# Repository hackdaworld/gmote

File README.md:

# GMote
[GMote](https://digidev.de/gmote) - The Generic LoRaWAN Node

GMote stands for Generic Mote.
It is meant to be a flexible (i.e. applicable in different scenarios for different purposes utilizing different sensors) IoT Node using the LoRa wireless data communication technology. 

The first test version was based on the Arduino Pro Mini, which requires very low power if you remove the LED and bypass the power regulator.
Once this proved to be a good idea, a slim version of the Mini Pro board (i.e. the ATMega 328PB) has been integrated and routed on the GMote circuit board.
At first, the Dragino LoRa Bee was the transceiving unit since we had good results with respect to range and usability.
In later versions, the relevant HopeRF modem (RFM95) chip was likewise integrated on the board due to availability and price. 

There are two PCB versions, a small and a mini version, which provide different amount of pin headers to connect various sensors or even actuators. 
Development of an ARM Cortex M0 based version is in progress.

The node is configurable via UART and (planned) LoRaWAN download frames.

It started within the Arduino framework and, as far as the AVR version is concerned, will stick to it to not loose the huge developer community.

## Most important

GMote is meant to become an all-purpose LoRaWAN node (and in fact a whole eco system).
Moreover, the design, hardware, firmware and software of the GMote project is open source and free to use without any restriction.
To enable everyone to participate, everything is kept as simple as possible, ranging from the low-level PCB design and firmware up to the high-level IoT platform app.

Since it aims to become a project for a hopefully huge community, let the GMote developers know what you think about it, about problems that occured, additional features that you require and everything you would like to have changed in the current realization. 
Anything on your mind?
Maybe to remove the RTC in favor of the internal watchdog timer to make the board even more simple (thereby accepting some inaccuracy in the periodicity of frames)? 
No I2C pinout or at least another version without?
A voltage regulator for a well defined supply but a shorter battery lifetime in return?
Whatever it is, let us know!

## Requirements

* ISP programmer, e.g. the [Pocket AVR Programmer](https://www.digikey.de/product-detail/de/sparkfun-electronics/PGM-09825/1568-1080-ND/5230949), to upload the firmware or an optional Arduino bootloader as you please.
* USB to serial converter (3.3V), e.g. the [FT231X Breakout](https://www.digikey.de/product-detail/de/sparkfun-electronics/BOB-13263/1568-1720-ND/7675364) for optionally uploading the firmware the Arduino way (via boot loader) and for serial communication and configuration. Strictly speaking, this is not required, since you could configure the node (i.e. program the EEPROM) via ISP. However, it is strongly suggested!
* A board (see below) produced by your favorite PCB manufacturer.
* The parts listed in the respective bill of materials.
* Soldering iron and solder.

## Hardware

### PCB

There are currently two versions ([small](pcb/small) and [mini](pcb/mini)) of the GMote LoRaWAN node, which are based on the ATMega 328PB and run quite reliably.
Moreover, there is one based on the [ARM MCU](pcb/arm), which is in very early stage and comes without any guarantee to work. We mean it!

You can find the available PCBs in the respective [PCB](pcb) directory
together with further details as well as the bill of materials and respective [DigiKey](https://www.digikey.de/) part numbers.

The boards are designed with [KiCad](http://kicad.org/).
A lot of PCB manufacturers directly support the KiCad PCB files.

The size of the SMD parts was chosen to be 0805 (2012) and hand soldering pads were used for the resistors and capacitors so you can DIY at home with a low cost soldering iron.
Caution: Patience required!

:warning: :warning:
The ATMega based boards are missing a pullup at the chipselect signal of the LoRa modem.
Please find details and a workaround in the [firmware section](#firmware).
:warning: :warning:

### Battery

The popular JST connector is used to connect the battery.
It is directly wired to VCC of the used ICs, no voltage regulator no polarity protection diodes!
Thus, be extremely careful when connecting your power supply.

GMote runs nicely with 3.7V LiPo batteries.
Higher voltages were not tested, so don't use higher voltages!
If you don't use the moisture or ultrasound distance sensor (these seem to require more than 3.3V), you can even run it with two AA(A) batteries (3V) or even accus (~2.8V).

## Firmware

All files can be found in the [firmware](firmware) location. 

### AVR ATMega 328PB fimrware

So far, you need the [Arduino IDE](https://www.arduino.cc/en/Main/Software) to build the firmware.
Moreover, the [LMIC library](https://github.com/matthijskooijman/arduino-lmic) is currently used to implement LoRaWAN.
Please follow the [instructions](https://github.com/matthijskooijman/arduino-lmic/#Installing) to include this library in your Arduino IDE.

Now you can build the firmware from the Arduino Sketch, [m328pb.ino](./firmware/mega328pb/m328pb.ino).\
Comment or uncomment the line
```c
#define PCB_MINI
```
in the very beginning of the sketch depending on the board you chose.

Alternatively, feel free to use one of the precompiled binaries.\
Mini: [m328pb_mini.hex](firmware/mega328pb/m328pb_mini.hex)\
Small: [m328pb_small.hex](firmware/mega328pb/m328pb_small.hex)

Since you build a GMote device from scratch, you start with a plain Atmega328P without an installed Arduino bootloader.
Use the ISP programmer and the [avrdude](https://www.nongnu.org/avrdude/) software to program either an optional Arduino bootloader or upload the GMote firmware directly.
To upload the firmware directly using the Pocket AVR Programmer, do
```
avrdude -patmega328pb -cusbtiny -v -Uflash:w:/path/to/m328pb_mini.hex:i
```
and adjust the path to the firmware hex file.
For disablinge the clock divider, which you have to do, run:
```
avrdude -patmega328pb -cusbtiny -v -Ulfuse:w:0xe2:m
```

:warning: :warning:
A pullup is required at the chipselect signal of the LoRa modem (pin 5 of the HopeRF or pin 14 of the ATMega).
Without it, programming the firmware or setting the fuse bits only works randomly because of the SPI LoRa modem disturbing the ISP programming process.
I am not sure why I didn't recognize this for the first few test devices.
Either there a different versions of the modem where some of them have an integrated pullup or it was simply by chance. 
I helped myself with a short wire applying VCC to the above mentioned pin during programming and setting the fuse bits.
There will be no board revision just fixing this bug since a new board is planned anyways.
Sorry for the inconvenience!
:warning: :warning:

### STM32F051 firmware

The version currently in development will be based on the *STM32F051K8T6* ARM Cortex M0 IC MCU operating at 48Mhz with 64KB FLASH and 8KB of embedded SRAM.

[Apache MyNewt](https://mynewt.apache.org/) as well as [Mbed OS](https://www.mbed.com/) are considered as an OS.

* MyNewt: First attempts can be found in [firmware/mynewt](firmware/mynewt) 
* Mbed OS: nothing yet ...

We keep you posted ...

## Sensors

Next to the very basic digital input sensing and ADC meassurements on the availabe IO and ADC pins, there are a couple of other sensors which require a slightly more special treatment.
At the moment, these are the ultrasound distance and the capacitive soil moisture sensor.

These are sensors you probably know already and where to buy them.
They were not designed by the GMote team.

However, in order to reduce costs and to simplify things, yet another soil moisture sensor based on the infamous *74HC14* hex inverting Schmitt trigger has been designed.
Here we go: [GMote Soil Moisture Sensor](pcb/sms).

## Utils and configuration

The GMote device is configured via the serial interface utilizing the USB to serial converter.
you can find the source code as well as installation and usage instructions in the [utils](utils) directory.

## Cases

To cover GMote and its sensors, a case was designed using [OpenSCAD](http://www.openscad.org/).
At the moment, the ultrasound distance and capacative moisture sensors are considered.

The image illustrates the idea of the case and sensors.
Details and files can be found in the [cases](cases) directory.

## Backend 

ToDo

## Software 

ToDo

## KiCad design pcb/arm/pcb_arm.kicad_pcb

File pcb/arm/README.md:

# GMote on ARM
[GMote](https://digidev.de/gmote) - Generic LoRaWAN Node

## Schematics

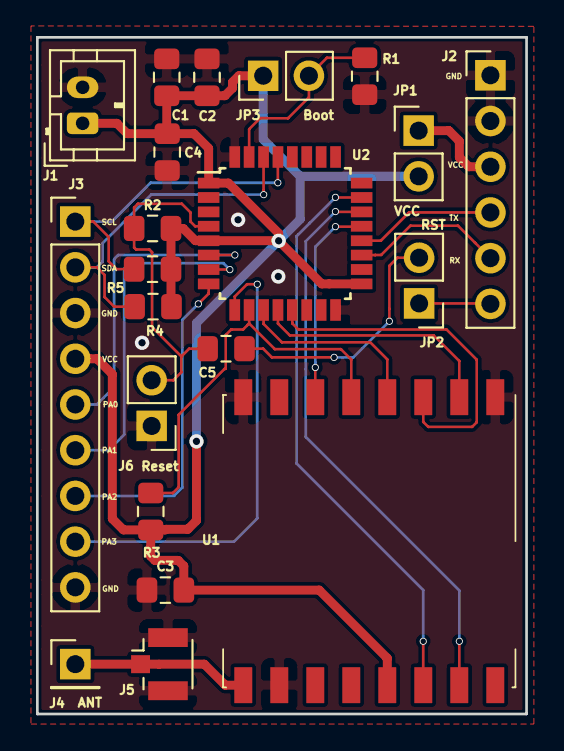
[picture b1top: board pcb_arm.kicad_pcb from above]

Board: 2 copper layers, 27.2 x 37.6 mm, 21 parts (0 on the bottom side), 23 nets.

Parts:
C1, C3, C4, C5: 100nF; C_0805_2012Metric_Pad1.15x1.40mm_HandSolder
C2: 10uF; C_0805_2012Metric_Pad1.15x1.40mm_HandSolder
J1: JST_POWER; JST_PH_B2B-PH-K_1x02_P2.00mm_Vertical
J2: 231X_Breakout; PinHeader_1x06_P2.54mm_Vertical
J3: IO_ADC_PINOUT; PinHeader_1x09_P2.54mm_Vertical
J4: ANT_WIRE; PinHeader_1x01_P2.54mm_Vertical
J5: Conn_Coaxial; U.FL_Hirose_U.FL-R-SMT-1_Vertical
J6: RST_PIN; PinHeader_1x02_P2.54mm_Vertical
JP1, JP2, JP3: Jumper; PinHeader_1x02_P2.54mm_Vertical
R1, R2, R3, R4, R5: 10k; R_0805_2012Metric_Pad1.15x1.40mm_HandSolder
U1: RFM95W-868S2; HOPERF_RFM9XW_SMD
U2: STM32F051K8Tx; LQFP-32_7x7mm_P0.8mm

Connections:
231X_RX: J2.5, U2.19
231X_TX: J2.4, U2.20
ANT: J4.1, J5.1, U1.9
ARM_BOOT0: JP3.2, R1.1, U2.31
ARM_RST: C5.1, J6.2, R2.1, U2.4
ARM_SCL: J3.1, R5.1, U2.29
ARM_SDA: J3.2, R4.1, U2.30
GND: C1.2, C2.2, C3.2, C4.2, J1.2, J2.1, J2.2, J3.3, J3.9, J5.2, J6.1, R1.2, U1.1, U1.8, U1.10, U2.16, U2.32
unnamed: J2.3, JP1.1
unnamed: J2.6, JP2.1
PA0: J3.5, U2.6
PA1: J3.6, U2.7
PA2: J3.7, U2.8
PA3: J3.8, U2.9
RFM95_DIO0: U1.14, U2.23
RFM95_DIO1: U1.15, U2.22
RFM95_RST: U1.6, U2.21
RST: C5.2, JP2.2
SPI_MISO: U1.2, U2.12
SPI_MOSI: U1.3, U2.13
SPI_NSS: R3.1, U1.5, U2.10
SPI_SCK: U1.4, U2.11
VCC: C1.1, C2.1, C3.1, C4.1, J1.1, J3.4, JP1.2, JP3.1, R2.2, R3.2, R4.2, R5.2, U1.13, U2.1, U2.5, U2.17

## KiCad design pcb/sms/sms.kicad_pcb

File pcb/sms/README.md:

# GMote soil moisture sensor

## Bill of materials

| Designator | Quantity  | Part            | DigiKey                        |
| ---------- | --------- | --------------- | ------------------------------ |
| R1         | 1         | R 0805 100k     |                                | 
| R2         | 1         | R 0805 100      |                                | 
| C1         | 1         | C 0805 10u      |                                | 
| J1         | 1         | Pin Header 2.54 |                                | 
| U1         | 1         | SOIC-14 74HC14  |                                | 

## Schematics

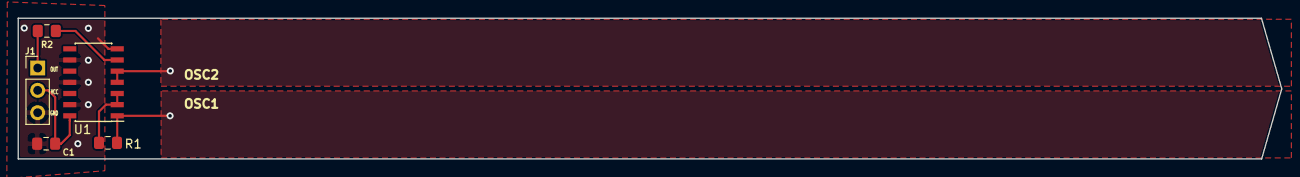
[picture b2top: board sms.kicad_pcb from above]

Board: 2 copper layers, 143.7 x 16.0 mm, 5 parts (0 on the bottom side), 7 nets.

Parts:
C1: 10u; C_0805_2012Metric_Pad1.15x1.40mm_HandSolder
J1: Conn_01x03_Male; PinHeader_1x03_P2.54mm_Vertical
R1: 100k; R_0805_2012Metric_Pad1.15x1.40mm_HandSolder
R2: 100; R_0805_2012Metric_Pad1.15x1.40mm_HandSolder
U1: 74HC14; SOIC-14_3.9x8.7mm_P1.27mm

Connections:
GND: C1.2, J1.3, U1.7, U1.9, U1.11, U1.13
unnamed: R1.1, U1.2, U1.3
unnamed: R2.2, U1.6
OSC1: R1.2, U1.1
OSC2: U1.4, U1.5
OUT: J1.1, R2.1
VCC: C1.1, J1.2, U1.14

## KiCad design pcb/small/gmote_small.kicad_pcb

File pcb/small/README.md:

# GMote Small
[GMote](https://digidev.de/gmote) - Small Version of the Generic LoRaWAN Node

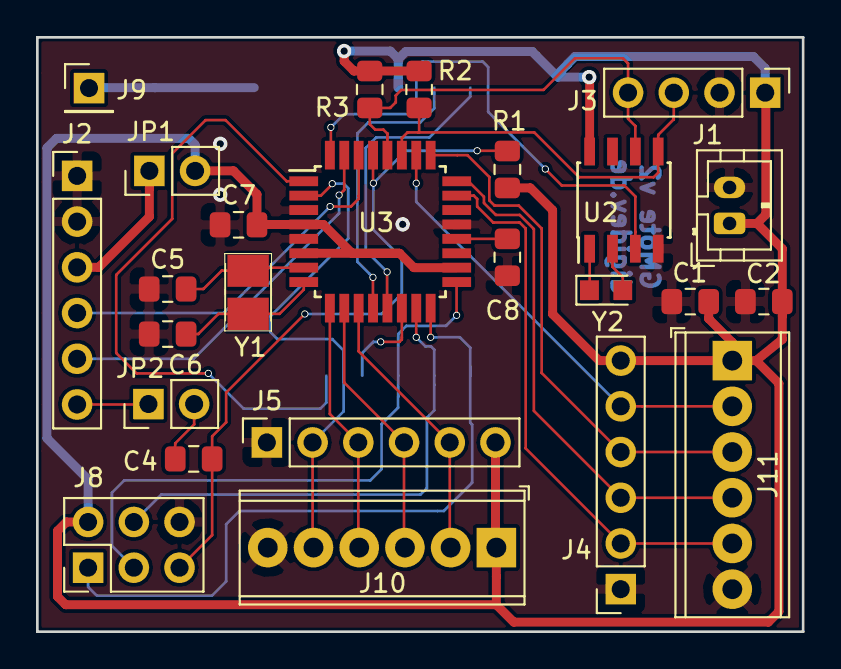
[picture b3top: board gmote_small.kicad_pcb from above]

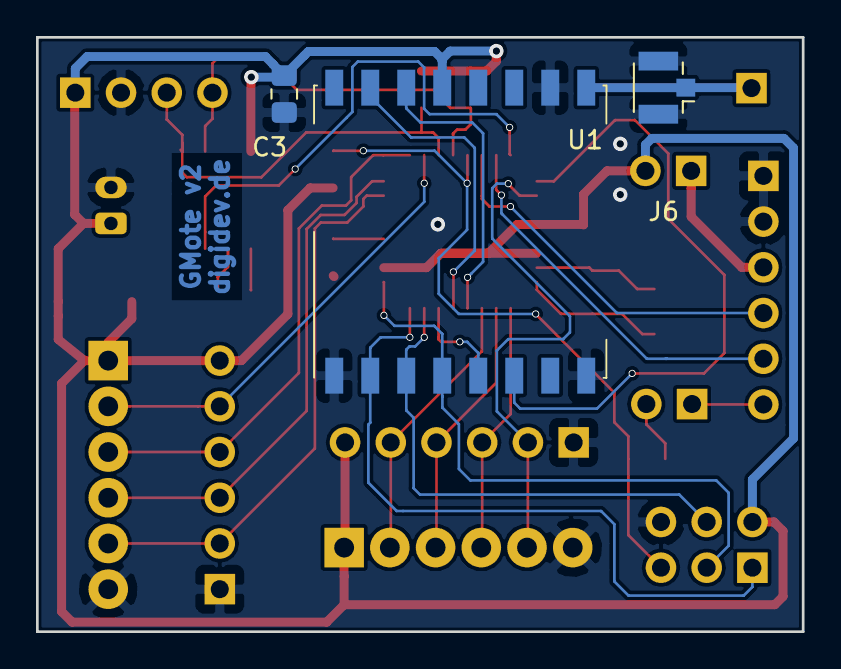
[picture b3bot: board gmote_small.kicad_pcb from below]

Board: 2 copper layers, 42.5 x 33.0 mm, 28 parts (3 on the bottom side), 32 nets.

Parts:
C1: 10uF; C_0805_2012Metric_Pad1.15x1.40mm_HandSolder
C2, C3, C4, C7, C8: 0.1uF; C_0805_2012Metric_Pad1.15x1.40mm_HandSolder
C5, C6: 16pF; C_0805_2012Metric_Pad1.15x1.40mm_HandSolder
J1: Conn_01x02_Male; JST_PH_B2B-PH-K_1x02_P2.00mm_Vertical
J2: Conn_01x06_Male; PinHeader_1x06_P2.54mm_Vertical
J3: Conn_01x04_Male; PinHeader_1x04_P2.54mm_Vertical
J4: Conn_ADC; PinSocket_1x06_P2.54mm_Vertical
J5: Conn_IO; PinSocket_1x06_P2.54mm_Vertical
J6: Ant_UFL; U.FL_Hirose_U.FL-R-SMT-1_Vertical
J8: AVR-ISP-6; PinHeader_2x03_P2.54mm_Vertical
J9: Conn_01x01_Male; PinHeader_1x01_P2.54mm_Vertical
J10: Screw_Terminal_IO; TerminalBlock_Phoenix_MPT-0,5-6-2.54_1x06_P2.54mm_Horizontal
J11: Screw_Terminal_ADC; TerminalBlock_Phoenix_MPT-0,5-6-2.54_1x06_P2.54mm_Horizontal
JP1, JP2: Jumper; PinHeader_1x02_P2.54mm_Vertical
R1, R2, R3: 10k; R_0805_2012Metric_Pad1.15x1.40mm_HandSolder
U1: RFM95W-868S2; HOPERF_RFM9XW_SMD
U2: PCF8563T; SOIC-8_3.9x4.9mm_P1.27mm
U3: ATmega328P-AU; TQFP-32_7x7mm_P0.8mm
Y1: 8Mhz; Crystal_3.0x2.5_HandSoldering
Y2: 32.768kHz; Crystal_SMD_2012-2Pin_2.0x1.2mm_HandSoldering

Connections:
ADC0: J4.2, J11.5, U3.23
ADC1: J4.3, J11.4, U3.24
ADC2: J4.4, J11.3, U3.25
ADC3: J4.5, J11.2, U3.26
ANT: J6.1, J9.1, U1.9
DTR: C4.1, JP2.2
GND: C1.2, C2.2, C3.1, C5.1, C6.1, C7.1, C8.2, J1.2, J2.1, J2.2, J3.2, J4.1, J5.1, J6.2, J8.6, J10.6, J11.6, U1.1, U1.8, U1.10, U2.4, U3.3, U3.5, U3.21
INT0: U2.3, U3.32
MISO: J8.1, U1.2, U3.16
MOSI: J8.4, U1.3, U3.15
unnamed: C8.1, U3.20
unnamed: J2.3, JP1.1
unnamed: J2.6, JP2.1
unnamed: U2.1, Y2.1
unnamed: U2.2, Y2.2
PB0: U1.14, U3.12
PB1: U1.15, U3.13
PD3: U1.6, U3.1
PD4: J5.2, J10.5, U3.2
PD5: J5.3, J10.4, U3.9
PD6: J5.4, J10.3, U3.10
PD7: J5.5, J10.2, U3.11
RXI: J2.4, U3.30
Reset: C4.2, J8.5, R1.1, U3.29
SCK: J8.3, U1.4, U3.17
SCL: J3.4, R3.2, U2.6, U3.28
SDA: J3.3, R2.2, U2.5, U3.27
SS: U1.5, U3.14
TXO: J2.5, U3.31
VCC: C1.1, C2.1, C3.2, C7.2, J1.1, J3.1, J4.6, J5.6, J8.2, J10.1, J11.1, JP1.2, R1.2, R2.1, R3.1, U1.13, U2.8, U3.4, U3.6, U3.18
XTAL1: C5.2, U3.7, Y1.1
XTAL2: C6.2, U3.8, Y1.2

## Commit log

2019-02-22 initial README
2019-02-26 initial commit of the small and mini GMote KiCad files
2019-03-29 added initial Readme files
2019-03-31 case + fw and utils dir
2019-04-01 new image
2019-04-01 cases
2019-04-01 added byttery info + schematic jpg
2020-02-21 added firmware
2020-02-21 formatting README
2020-02-21 STM update
2020-02-21 added selfmade soil moisture sensor
2020-02-21 added arm pcb
2020-02-21 pcb arm README added
2020-04-14 initial checkin of first mynewt porting attempts
2020-04-14 deleted irrelevant targets
2020-04-27 explaining a bug and its workaround
2021-11-08 Update README.md
    https://forum.kicad.info/t/warning-avoid-all-links-to-kicad-pcb-org-use-kicad-org/31521
